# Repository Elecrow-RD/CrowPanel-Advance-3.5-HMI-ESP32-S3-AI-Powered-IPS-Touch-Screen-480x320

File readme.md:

## Menu
### 1, Product picture
### 2, Product version number
### 3, product information
### 4, Use the driver module
### 5,Quick Start
### 6,Folder structure.
### 7,Pin definition
### 8,Guidelines for downloading some of the files from the github repository

### 1, Product picture

### 2, Product version number

|      | Hardware | Software | Remark |
| ---- | -------- | -------- | ------ |
| 1    | V1.0     | V1.0     | old |
| 2    | V1.2     | V1.2     | old |
| 3    | V1.3     | V1.3     | old |
| 4    | V1.4     | V1.3     | latest |

### Version update points:

**V1.2 upgraded**, optimized the amplifier circuit, better sound quality, and use IO21 to control mute. i2s_mic changed to two pins IO9 and IO10 control.

**Version 1.3**,Only the button component has been updated. All other hardware and I/O pins remain the same as in the previous version.

**Version 1.4** is simply an update to the previous version that modifies the packaging of the touchscreen FPC connector. There are no other differences.

### 3, product information

| Main Chip-ESP32-S3-WROOM-1-N16R8     |                                                              |
| -------------------------------------------- | ------------------------------------------------------------ |
| CPU/SoC                                      | high-performance Xtensa 32-bit LX7 dual-core processor, with up to 240MHz |
| System Memory                                | 512KB SRAM、8M PSRAM                                         |
| Memory                                       | 16M Flash，384KB ROM                                         |
| Development Language                         | MicroPython、C/C++                                           |
| Development Environment                      | ESP-IDF、Arduino IDE、PlatformIO、Micro Python         |
| **Screen**                                   |                                                              |
| Size                                         | 3.5 inch                                                     |
| Diver IC                                     | ILI9488                                                      |
| Resolution                                   | 480*320                                                      |
| Display Panel                                | IPS Panel                                                    |
| Touch Panel                                  | Capacitive Single Touch                                      |
| Viewing Angle                                | 178°                                                         |
| Brightness                                   | 400 cd/m²(Typ.)                                              |
| Color Depth                                  | 16-bit                                                       |
| **Wireless Communication - Onboard Antenna** |                                                              |
| WiFi                                         | Support 2.4GHz, 802.11a/b/g/n                                |
| Bluetooth                                    | Support Bluetooth 5.0 and BLE                                |
| Other                                        | **LoRa**                                                     |
| **Interface/Function**                       |                                                              |
| Interface                                    | USB port, UART, I2C, SD card slot, battery socket, speaker port, microphone, etc. |
| Function                                     | RTC clock, audio amplifier, volume control, battery charge management, USB to UART, etc. |
| **Button/LED Indicator**                     |                                                              |
| Reset Button                                 | Yes, press to reset the device                               |
| Boot Button                                  | Yes, press and hold the power button to burn the program     |
| PWR                                          | Power indicator                                              |
| CHG                                          | Lithium battery charging status, completion indication       |
| **Other**                                    |                                                              |
| Installation method                          | Back hanging, fixed hole                                     |
| Operating temperature                        | -20~70 °C                                                    |
| Storage temperature                          | -30~80 °C                                                    |
| Power Input                                  | 5V/2A, USB or UART terminal                                  |
| Dimensions                                   | 101.4\*63.3*15.8mm                                            |

### 4, Use the driver module

| Name   | dependency library                      |
| ------ | --------------------------------------- |
| LVGL   | lvgl/lvgl@8.3.3                         |
| ST7789 | Adafruit GFX Library<br/>version=1.11.0 |

### 5,Quick Start
### Arduino IDE starts

#### Teaching Case Path：./example/example_code3.5

1.Download the library files used by this product to the 'libraries' folder.

C:\Users\Documents\Arduino\libraries\

2.Open the Arduino IDE

3.Open the code configuration environment and burn it

### ESP-IDF starts

#### Teaching Case Path：./example/idf_code

1.Right-click on an empty space in the project folder and select "Open with VS Code" to open the project.

2.In the IDF plug-in, select the port, then compile and flash

### 6,Folder structure.

|--3D file： Contains 3D model files (.stp) for the hardware. These files can be used for visualization, enclosure design, or integration into CAD software.

|--Datasheet: Includes datasheets for components used in the project, providing detailed specifications, electrical characteristics, and pin configurations.

|--Eagle_SCH&PCB: Contains **Eagle CAD** schematic (`.sch`) and PCB layout (`.brd`) files. These are used for circuit design and PCB manufacturing.

|--example: Provides example code and projects to demonstrate how to use the hardware and libraries. These examples help users get started quickly.

|--factory_firmware: Stores pre-compiled factory firmware that can be directly flashed onto the device. This ensures the device runs the default functionality.

|--factory_sourcecode:  Contains the source code for the factory firmware, allowing users to modify and rebuild the firmware as needed.

|--libraries: Includes necessary libraries required for compiling and running the project. These libraries provide drivers and additional functionalities for the hardware.

|--Squareline_studio Instructions for use: Squareline_studio instructions: Demonstrate the use of squareline studio.

### 7,Pin definition

SPIClass* hspi = nullptr;
#define HSPI_MISO  4
#define HSPI_MOSI  6
#define HSPI_SCLK  5
#define HSPI_SS    19

#define SD_MOSI 6
#define SD_MISO 4
#define SD_SCK  5
#define SD_CS   7 //The chip selector pin is not connected to IO

#define I2S_DOUT 12
#define I2S_BCLK 13
#define I2S_LRC 11

cfg.pin_sclk = 42;  // SPIのSCLK

cfg.pin_mosi = 39;  // SPIのCLK

cfg.pin_miso = -1;  // SPIのMISO

cfg.pin_dc = 41; 

#define TOUCH_GT911_SCL 16
#define TOUCH_GT911_SDA 15

### 8,Guidelines for downloading some of the files from the github repository

##### 1, open the link in your browser: https://downgit.github.io/

##### 2, paste the URL of the GitHub destination folder in the input box (example format: `https://github.com/username/repository name/tree/branch name/folder path`)

##### 3, even a that way to download the file.

①Click the “Create Download Link” button to create a download link, copy the link and open it with your browser to download the contents of the corresponding folder directly.

②Click Download, and you can also download it directly.

#### Note: DownGit downloads are stored by default in **your browser's default downloads folder**, usually:

- **Windows**: `C:\Users\your username\Downloads\` (downloads folder)
- **macOS**: `~/Downloads/` (downloads folder)
- **Linux**: `~/Downloads/` (Downloads folder)

If you change the default download path in your browser, the file will be stored in the download location you set. You can find the downloaded file path in your browser's **Download History** (shortcut `Ctrl + J` or `Cmd + J`).

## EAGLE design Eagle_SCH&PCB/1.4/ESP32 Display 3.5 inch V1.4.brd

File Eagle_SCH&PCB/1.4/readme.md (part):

# 3.5-Inch ESP32-S3 Hardware Driver Guide

| Item | Details |
|---|---|
| Document Version | V1.0 |
| Date | 2026-07-30 |
| Author | OpenAI Codex (compiled from project materials) |
| Applicable Hardware | 3.5-inch ESP32 Display / CrowPanel Advance HMI boards |
| Hardware References | `1.4/ESP32 Display 3.5 inch V1.4.sch`, `.brd`, and `ESP32-Display-3.5-inch-V1.4.pdf` |
| Software References | Board-level examples from `lesson-01` through `lesson-08` under `3.5_Arduino` (excluding examples bundled with third-party libraries) |
| Determination Principle | When the schematic conflicts with code that has been successfully tested, the project’s board-level example code takes precedence, and the discrepancy is documented |

> **Important Version Notice**: The directories and filenames identify the hardware as **V1.4**, but the title block in the Eagle schematic and the internal title in the PDF identify it as **V1.2**. This document describes the materials currently available in the repository and does not claim that the two versions are electrically identical. Before production, repair, or porting, the board revision must be confirmed from the PCB silkscreen and/or physical measurements.

## 1. Evidence Levels and Usage

| Level | Meaning | Usage Recommendation |
|---|---|---|
| A - Code Verified | The project’s board-level examples contain explicit pin assignments and success/failure criteria or visible functionality | Use as the primary reference for maintenance and porting |
| B - Schematic and Code Consistent | The schematic nets match the code, but the examples do not cover all edge cases | Usable, but integration testing with the target firmware is still required |
| C - Schematic Confirmed | The component/net exists in the schematic, but the repository contains no corresponding board-level driver test case | Do not claim software verification; additional testing is required |
| D - External Module Example | The code verifies a module connected to an expansion port, not an onboard component | Enable only when the same external module is installed |

“Verified” in this document only means that the repository provides runnable examples and explicit configurations for this board. It does not mean that the physical board was reflashed during the creation of this document.

## 2. System Architecture and Software Stack

- MCU: ESP32-S3-WROOM-1, identified in the schematic as `ESP32-S3-N16R8` (board-level designation indicating 16 MB Flash and 8 MB PSRAM).
- Framework: Arduino-ESP32, supported at the lower level by ESP-IDF peripheral drivers (SPI/I2C/I2S/UART, DMA, and PSRAM). No bare-metal register operations are used.
- Graphics: LovyanGFX + LVGL 9.1.0; LVGL uses two full-screen RGB565 buffers in PSRAM.
- Storage: Arduino `FS`/`SD` on a dedicated SPI bus.
- Audio: ESP32-audioI2S 3.0.12 + Wi-Fi, with output to the onboard NS4168.
- Wireless Expansion: RF24 1.6.1 (nRF24L01) and RadioLib 7.1.0 (SX1262/LoRaWAN).
- Sensor Expansion: Crowbits_DHT20; separate GT911 driver code is also provided for touch input.
- RTOS: Arduino-ESP32 runs FreeRTOS internally, but the project examples do not create custom tasks, queues, or synchronization objects.

## 3. Peripheral Overview

| Category | Peripheral/Component | Key Interface and GPIOs | Status |
|---|---|---|---|
| MCU | ESP32-S3-WROOM-1 | Native USB GPIO19/20; UART0; multiple multiplexed peripherals | B |
| Display | 3.5-inch TFT, configured as ILI9488 in code | SPI2: SCLK42, MOSI39, DC41, CS40; RST2; BL38 | A; RST conflict between schematic and code |
| Touch | Configured as GT911 in code | I2C0: SDA15, SCL16; INT47, RST48; 0x14/400 kHz | A; controller model not identified in schematic |
| Storage | microSD/TF (J5) | MISO4, SCLK5, MOSI6, CS7; SPI at 80 MHz | A/B |
| Audio Output | NS4168 + speaker connector J12 | I2S: LRCLK11, BCLK13, DOUT12; CTRL21 | A/B |
| Microphone | Digital I2S/PDM MIC (MIC1) | CLK9, DATA10; GPIO45 selects the switch path | C |
| Analog Switch | SGM3799 | GPIO9/10 multiplexed between MIC and wireless SPI; SEL=GPIO45 | B |
| Buzzer | Passive buzzer B1 + SS8050 | GPIO8 through NPN low-side driver | C |
| RTC | PCF8563/BM8563 + CR1220 | SDA15, SCL16; common address 0x51 (not verified by code) | C |
| USB-UART | CH340K + automatic download circuit | UART0; DTR/RTS drive EN/BOOT | C (hardware function) |
| Native USB/OTG | Type-C J2 | D-=GPIO19, D+=GPIO20 (through 0 Ω configuration positions) | C |
| USB-UART/Power | Type-C J1 | CH340K USB data, 5 V input | C (hardware function) |
| Battery Charging | TP4059 + PH2.0 battery connector J3 | Autonomous hardware operation; PROG=2 kΩ; CHRG/DONE indicators managed by U14 | C |
| Power Boost | RY3420/HM3416H | Autonomous hardware operation; 45.3 kΩ/10 kΩ feedback; EN connected to VIN | C |
| Charging Indicator Control | STC8G1K08 + red/green LEDs | Monitors CHRG/DONE; not an ESP32-programmable interface | C |
| Backlight/Display Power | NPN backlight switch, optional TFT power switch | BL=GPIO38, active high; GPIO14 path marked NC | A/C |
| Buttons | BOOT K3, RESET K4 | BOOT=GPIO0 active low; RESET=EN active low | C (hardware function) |
| I2C Expansion | J13 HY2.0 | SCL16, SDA15, 3V3, GND | B; shares bus with RTC/touch |
| UART1 Expansion | J15 HY2.0 | ESP TX=GPIO17, ESP RX=GPIO18, 3V3, GND | C |
| UART0 Expansion | J10 | RXD0_H, TXD0_H, 5V, GND | C; shared with download and logging |
| Wireless SPI Expansion | J9/J11 | SCLK10, MISO9, MOSI3, CS0, BUSY46, 3V3/GND | B/D |
| External UART Module | Zigbee example | RX2, TX1, 115200 8N1; GPIO45=LOW | D; multiplexing risk with LCD RST/wireless control |
| External Sensor | DHT20 | I2C SDA15/SCL16; 200 ms read interval | D |
| External Actuator | lesson-03/05 lamp or LED | GPIO18, push-pull output | D; conflicts with UART1 RX |
| External nRF24L01 | RF24 example | SCLK10/MISO9/MOSI3, CE1, CSN2; GPIO45=LOW | D |
| External SX1262 | LoRaWAN example | SCLK10/MISO9/MOSI3, NSS0, DIO1=1, RST2, BUSY46 | D |

## 4. Authoritative GPIO Mapping

| GPIO | Schematic Net/Function | Usage in Successfully Tested Code | Electrical/Multiplexing Notes |
|---:|---|---|---|
| 0 | Wireless CS, BOOT button | SX1262 NSS | Boot strapping pin; a low level from the button affects startup and SPI transactions |
| 1 | UART2 TX net | nRF24 CE; SX1262 DIO1; Zigbee TX | Mutually exclusive across examples; do not initialize simultaneously |
| 2 | UART2 RX net | LCD RST; nRF24 CSN; SX1262 RST; Zigbee RX | Primary conflict point; code takes precedence, but each function requires exclusive use |
| 3 | Wireless SPI MOSI | nRF24/SX1262 MOSI | GPIO45 must select the wireless path |
| 4 | SD MISO | SD MISO | Input with onboard 10 kΩ pull-up |
| 5 | SD SCLK | SD SCLK | Push-pull clock |
| 6 | SD MOSI | SD MOSI | Push-pull data with onboard 10 kΩ pull-up |
| 7 | SD CS | SD CS | Push-pull, idle high, with onboard 10 kΩ pull-up |
| 8 | BEEP | No code | PWM/LEDC recommended; driven through an NPN transistor; polarity and frequency require physical verification |
| 9 | MIC CLK / wireless MISO (SGM3799 COM) | nRF24/SX1262 MISO | Selected by GPIO45; audio recording and wireless SPI cannot be used simultaneously |
| 10 | MIC DATA / wireless SCLK (SGM3799 COM) | nRF24/SX1262 SCLK | Same as above |
| 11 | I2S LRCLK | Audio LRCLK | Push-pull output |
| 12 | I2S SDIN (amplifier data input) | Audio DOUT | Named DOUT in code from the ESP32’s perspective |
| 13 | I2S BCLK | Audio BCLK | Push-pull output |
| 14 | TFT_PWR (components marked NC) | No code | Do not rely on this unless BOM installation of Q11/Q12/R52/R53/R61 is confirmed |
| 15 | I2C SDA | GT911, DHT20, RTC, J13 | Open-drain; schematic shows a 4.7 kΩ pull-up to 3.3 V |
| 16 | I2C SCL | GT911, DHT20, RTC, J13 | Open-drain; schematic shows a 4.7 kΩ pull-up to 3.3 V |
| 17 | UART1 TX | No board-level UART1 example provided | J15 uses 3.3 V logic |
| 18 | UART1 RX | Push-pull output for external lamp/LED | Cannot be used as UART1 RX while GPIO18 is used for the lamp |
| 19 | USB D- | USB Serial/JTAG or OTG | Native USB differential line; do not use as a general-purpose GPIO |
| 20 | USB D+ | USB Serial/JTAG or OTG | Native USB differential line; do not use as a general-purpose GPIO |
| 21 | NS4168 control | Audio amplifier control: initially HIGH, then LOW before playback | Code proves LOW is the operating state; do not assume a conventional active-high EN when porting |
| 38 | LCD backlight | `OUTPUT` + `HIGH` turns it on | Active high through an SS8050 switch; PWM dimming is possible but the frequency must be verified |
| 39 | TFT SDA/MOSI | LCD MOSI | Write-only, no MISO |
| 40 | TFT CS | LCD CS | Push-pull, idle high |
| 41 | TFT RS/D-C | LCD DC | Push-pull |
| 42 | TFT SCK | LCD SCLK | SPI2, 40 MHz writes |
| 45 | SPI/MIC analog switch select | Wireless examples set it to `LOW` | LOW selects the wireless path and disconnects the microphone; stop the bus/microphone clock before changing the level |
| 46 | BOOT_BUSY | SX1262 BUSY; SS placeholder for the nRF24 SPI object | ESP32-S3 boot strapping pin; peripheral power-up levels must not interfere with startup |
| 47 | TP_INT | GT911 INT | Used by LovyanGFX; the auxiliary `touch.h` version sets it to -1 |
| 48 | TP_RST | GT911 RST | Used by LovyanGFX; the auxiliary `touch.h` version sets it to -1 |

## 5. Detailed Onboard Peripheral Descriptions

### 5.1 ESP32-S3 MCU, Flash/PSRAM, and Boot

The schematic component is an ESP32-S3-WROOM-1, with N16R8 shown in the drawing text. The project uses the Arduino API, ESP-IDF SPI/I2C driver types, and `heap_caps_malloc(..., MALLOC_CAP_SPIRAM)`, so the display firmware depends on functional PSRAM.

- Download UART: UART0 connects to the CH340K through a BSS138 level-shifting/isolation network; J10 also exposes `RXD0_H/TXD0_H`.
- Automatic Download: The CH340K’s DTR/RTS signals drive GPIO0/EN through U10.
- Manual Buttons: K3 pulls GPIO0 low (BOOT); K4 pulls EN low (RESET).
- Native USB: GPIO19/20 correspond to D-/D+ and connect to Type-C J2 through 0 Ω configuration positions.
- Serial Examples: lesson-01 uses `Serial.begin(9600)`; most other examples use 115200. Standardize the baud rate when porting to avoid mistaking garbled logs for a hardware failure.

```cpp
Serial.begin(115200);
// PSRAM for the display: each 480x320 RGB565 buffer is approximately 307200 bytes
buf = (lv_color_t *)heap_caps_malloc(sizeof(lv_color_t) * 480 * 320,
                                     MALLOC_CAP_SPIRAM);
```

### 5.2 ILI9488 TFT Display and Backlight

The code explicitly instantiates `lgfx::Panel_ILI9488` using SPI2_HOST, mode 0, and automatic DMA channel selection. The panel’s native memory orientation is 320x480, while the application uses a logical landscape resolution of 480x320.

| Signal | GPIO | Configuration |
|---|---:|---|
| SCLK | 42 | SPI2, 40 MHz write, 16 MHz configured read |
| MOSI/SDA | 39 | Unidirectional write |
| MISO | -1 | Disabled, `readable=false` |
| D/C | 41 | GPIO push-pull |
| CS | 40 | GPIO push-pull |
| RST | 2 (code) | Does not match the schematic; see the conflict matrix |
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
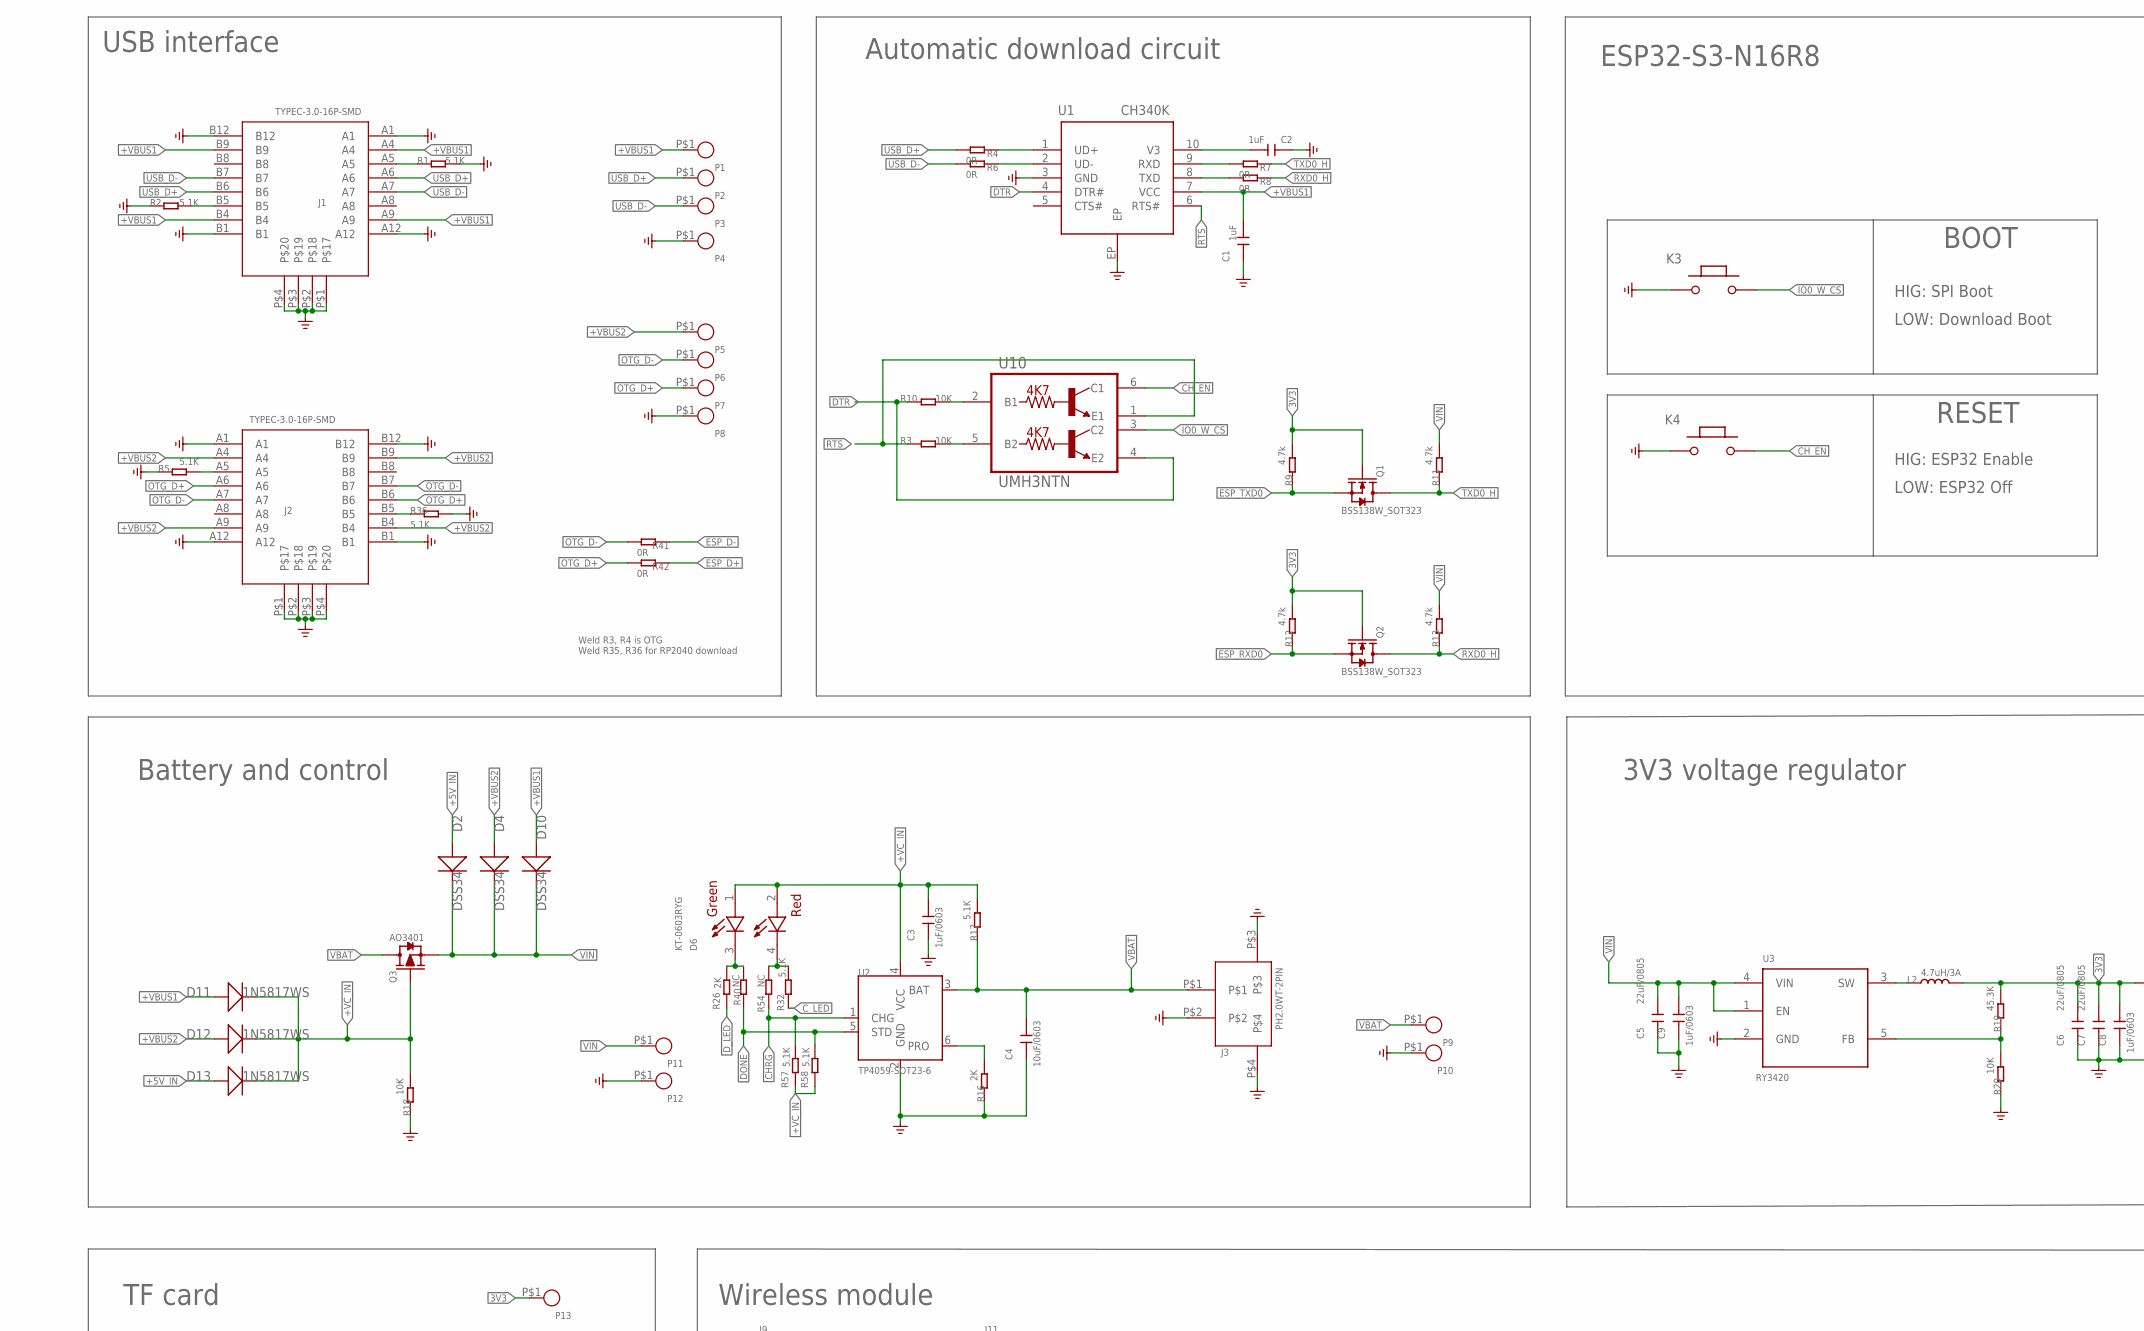
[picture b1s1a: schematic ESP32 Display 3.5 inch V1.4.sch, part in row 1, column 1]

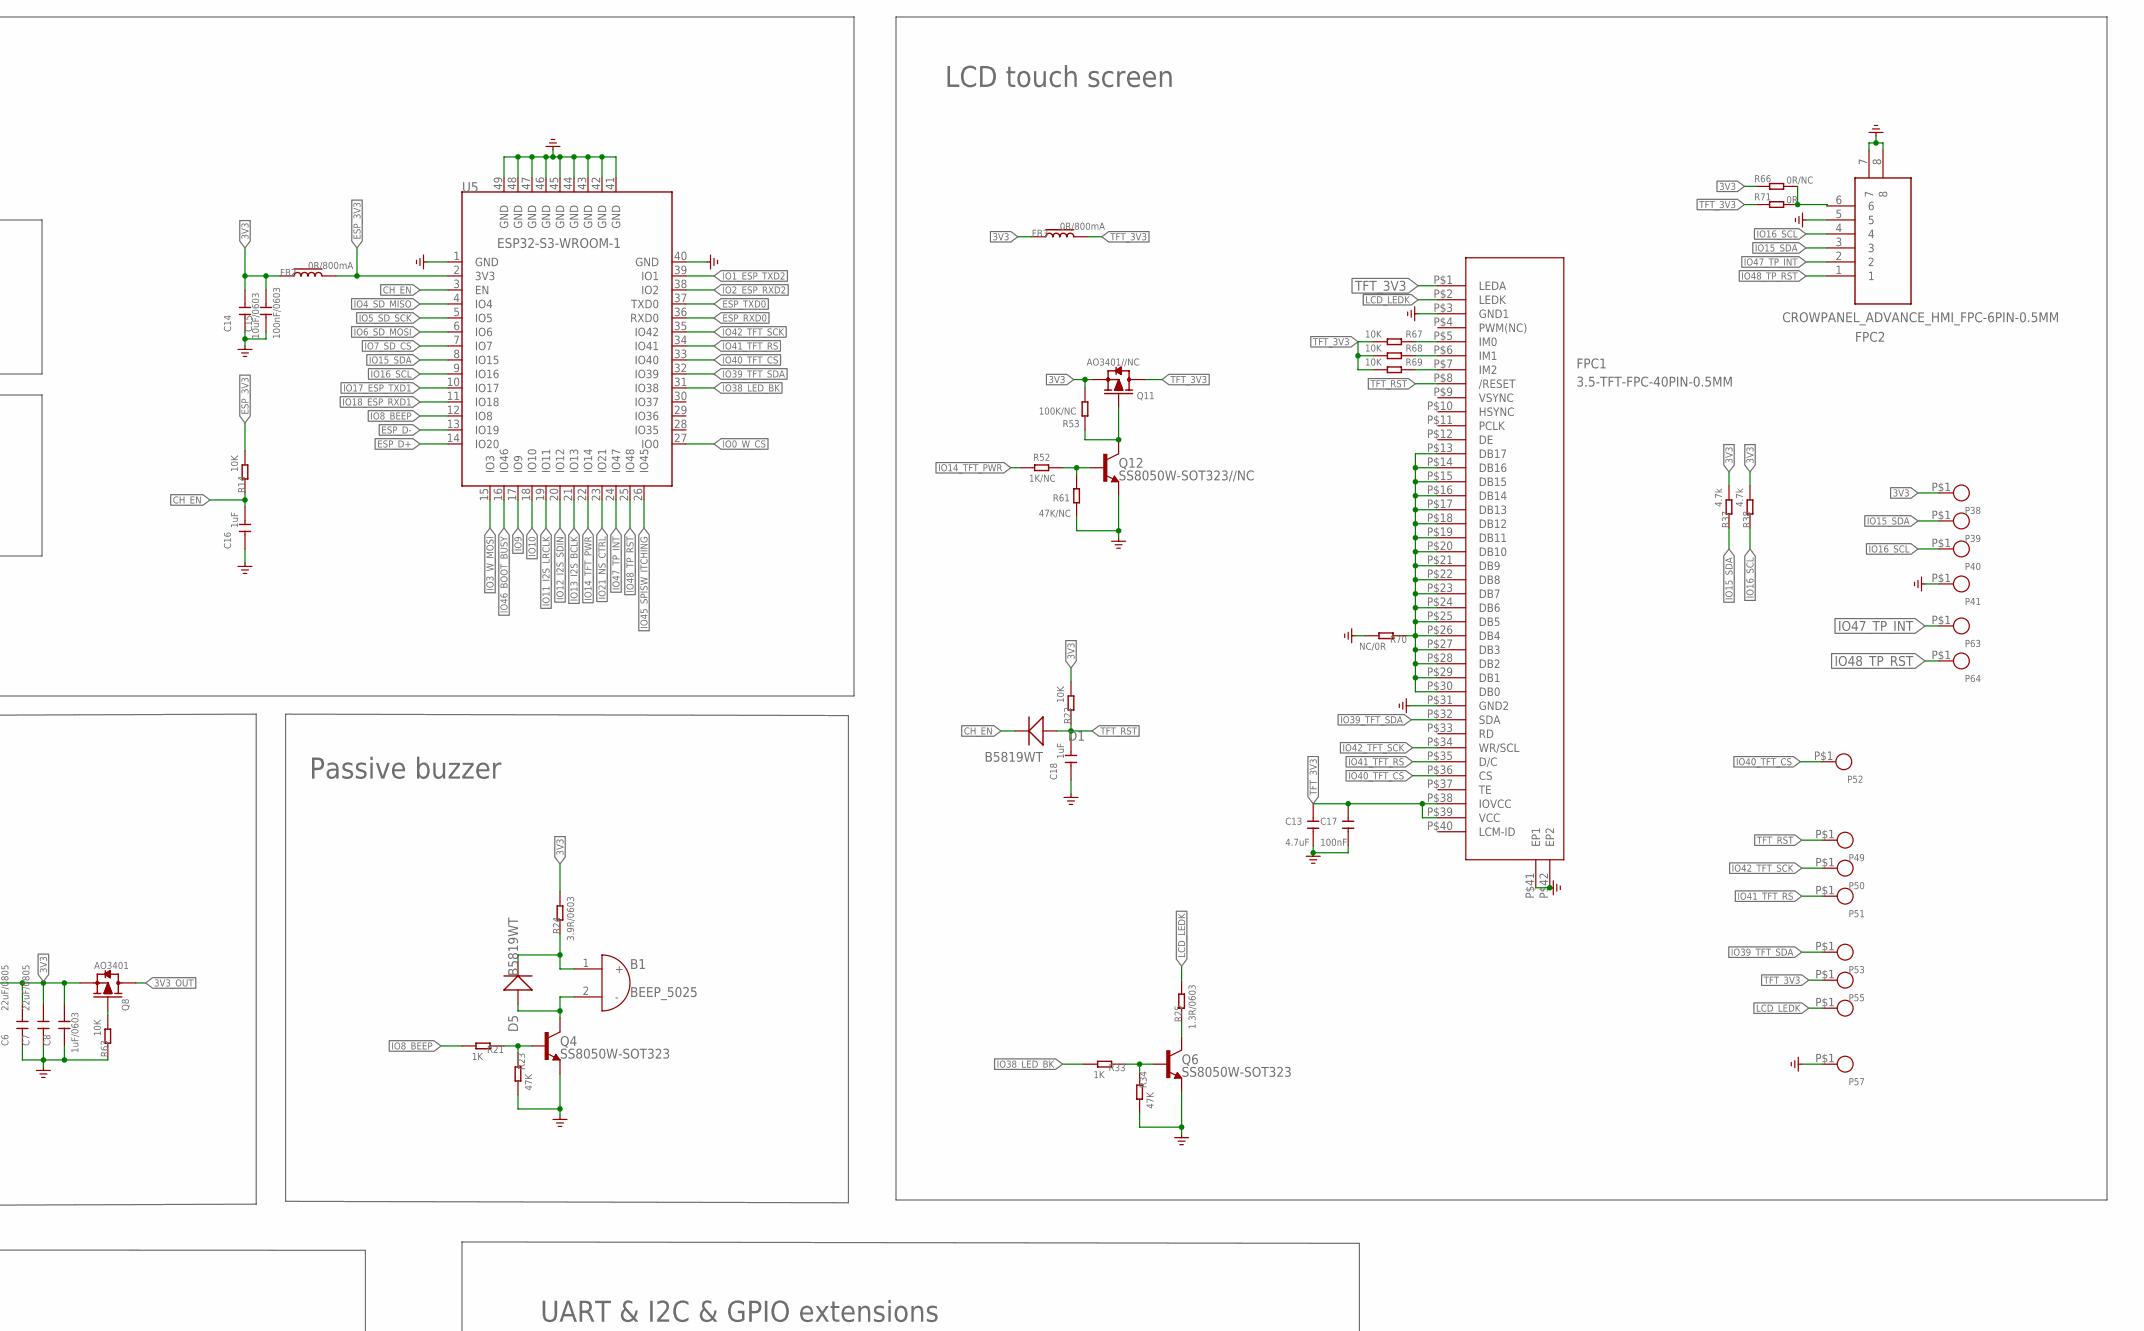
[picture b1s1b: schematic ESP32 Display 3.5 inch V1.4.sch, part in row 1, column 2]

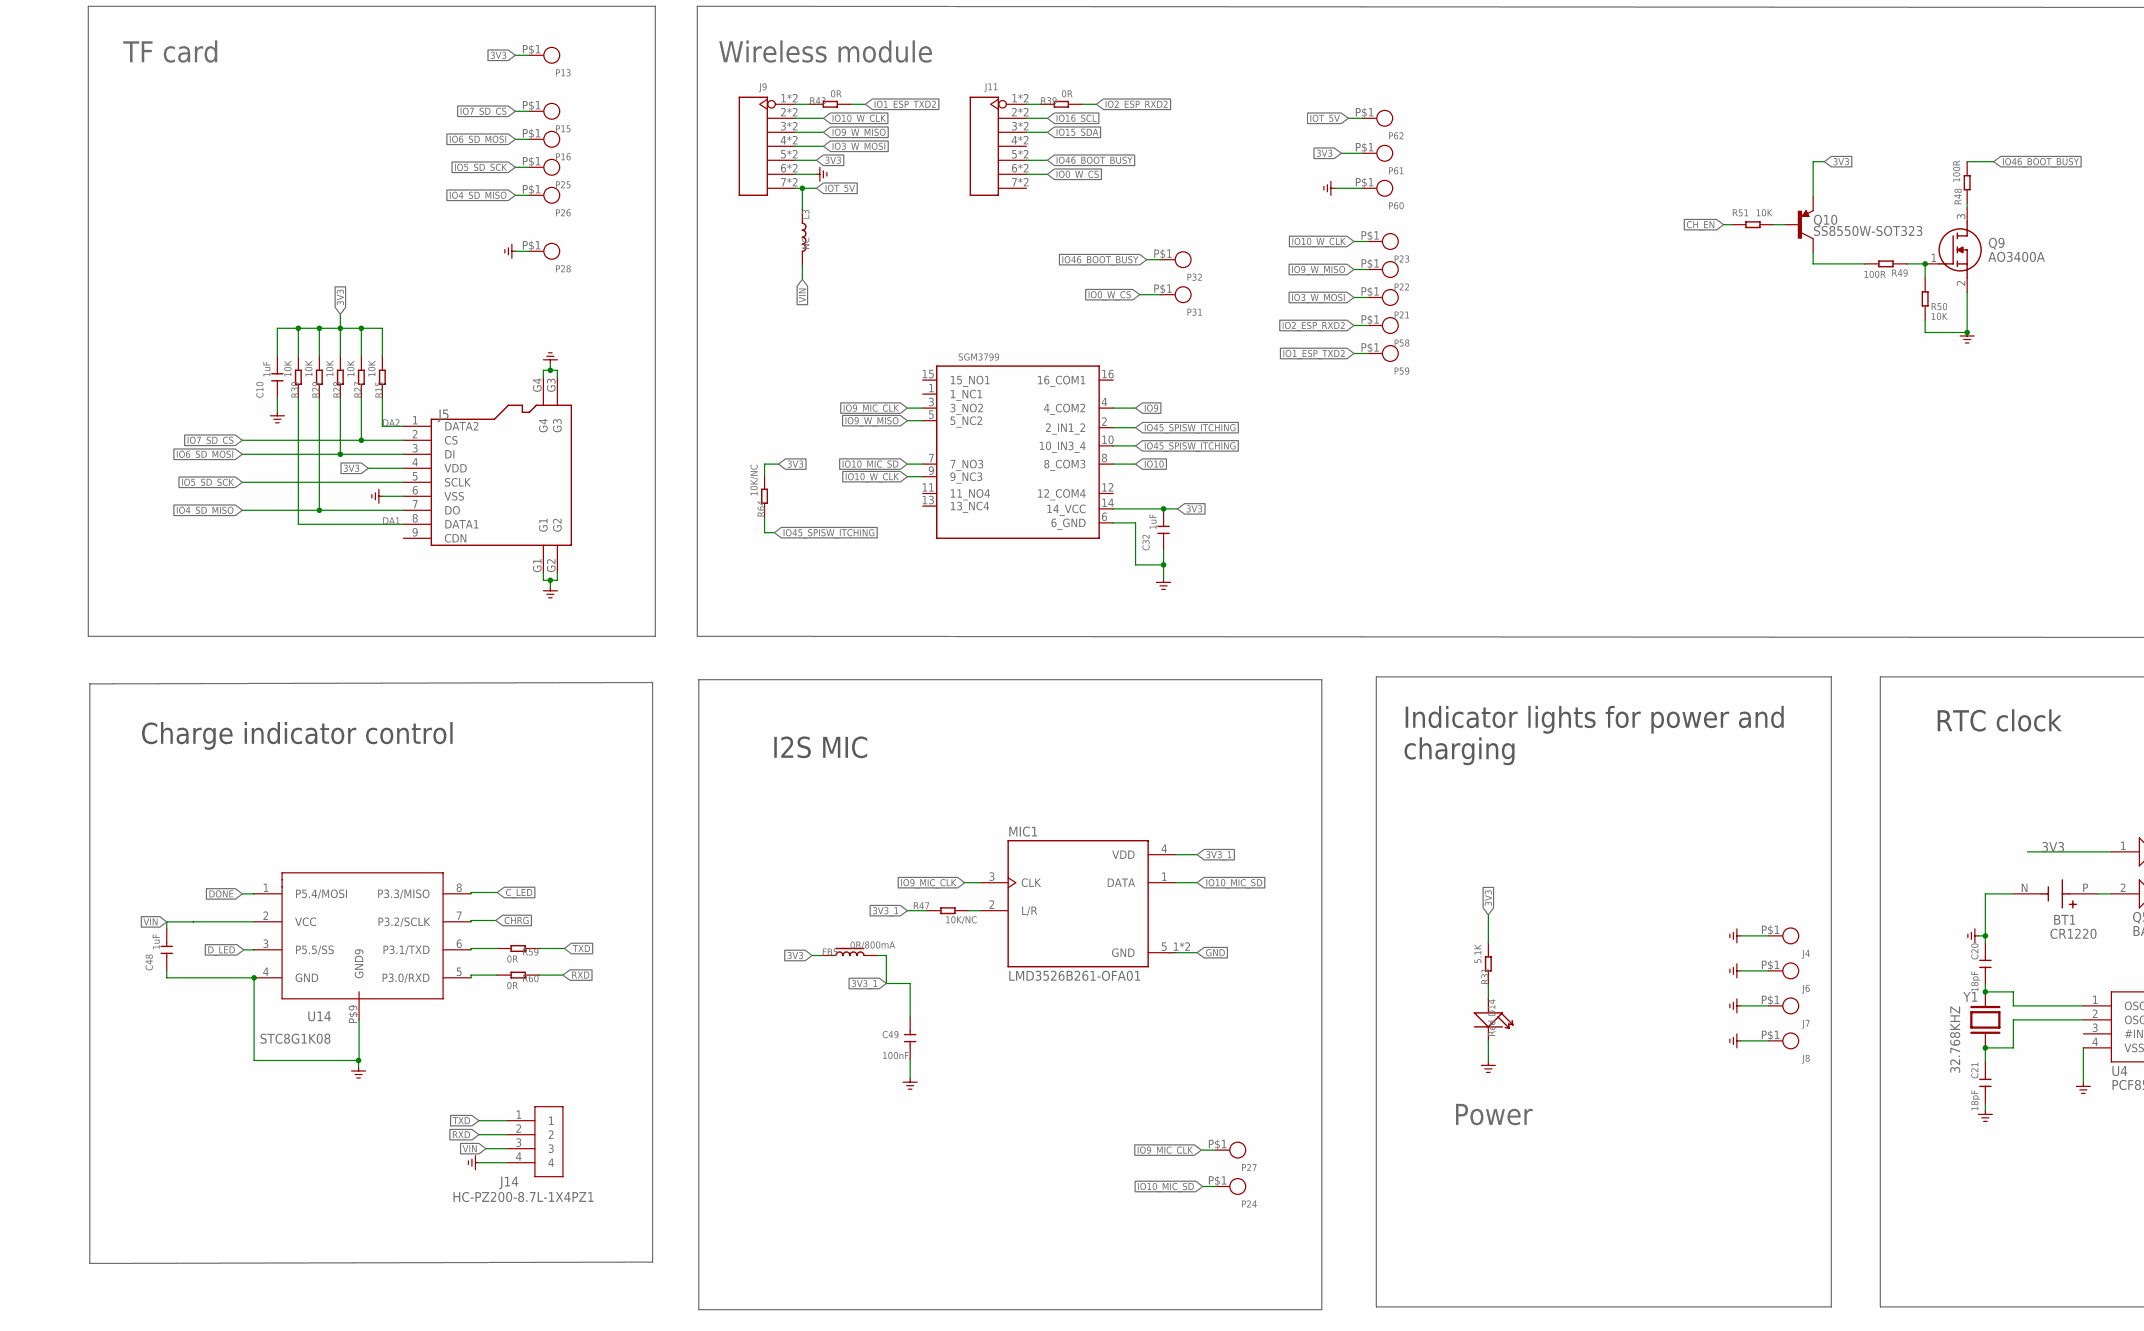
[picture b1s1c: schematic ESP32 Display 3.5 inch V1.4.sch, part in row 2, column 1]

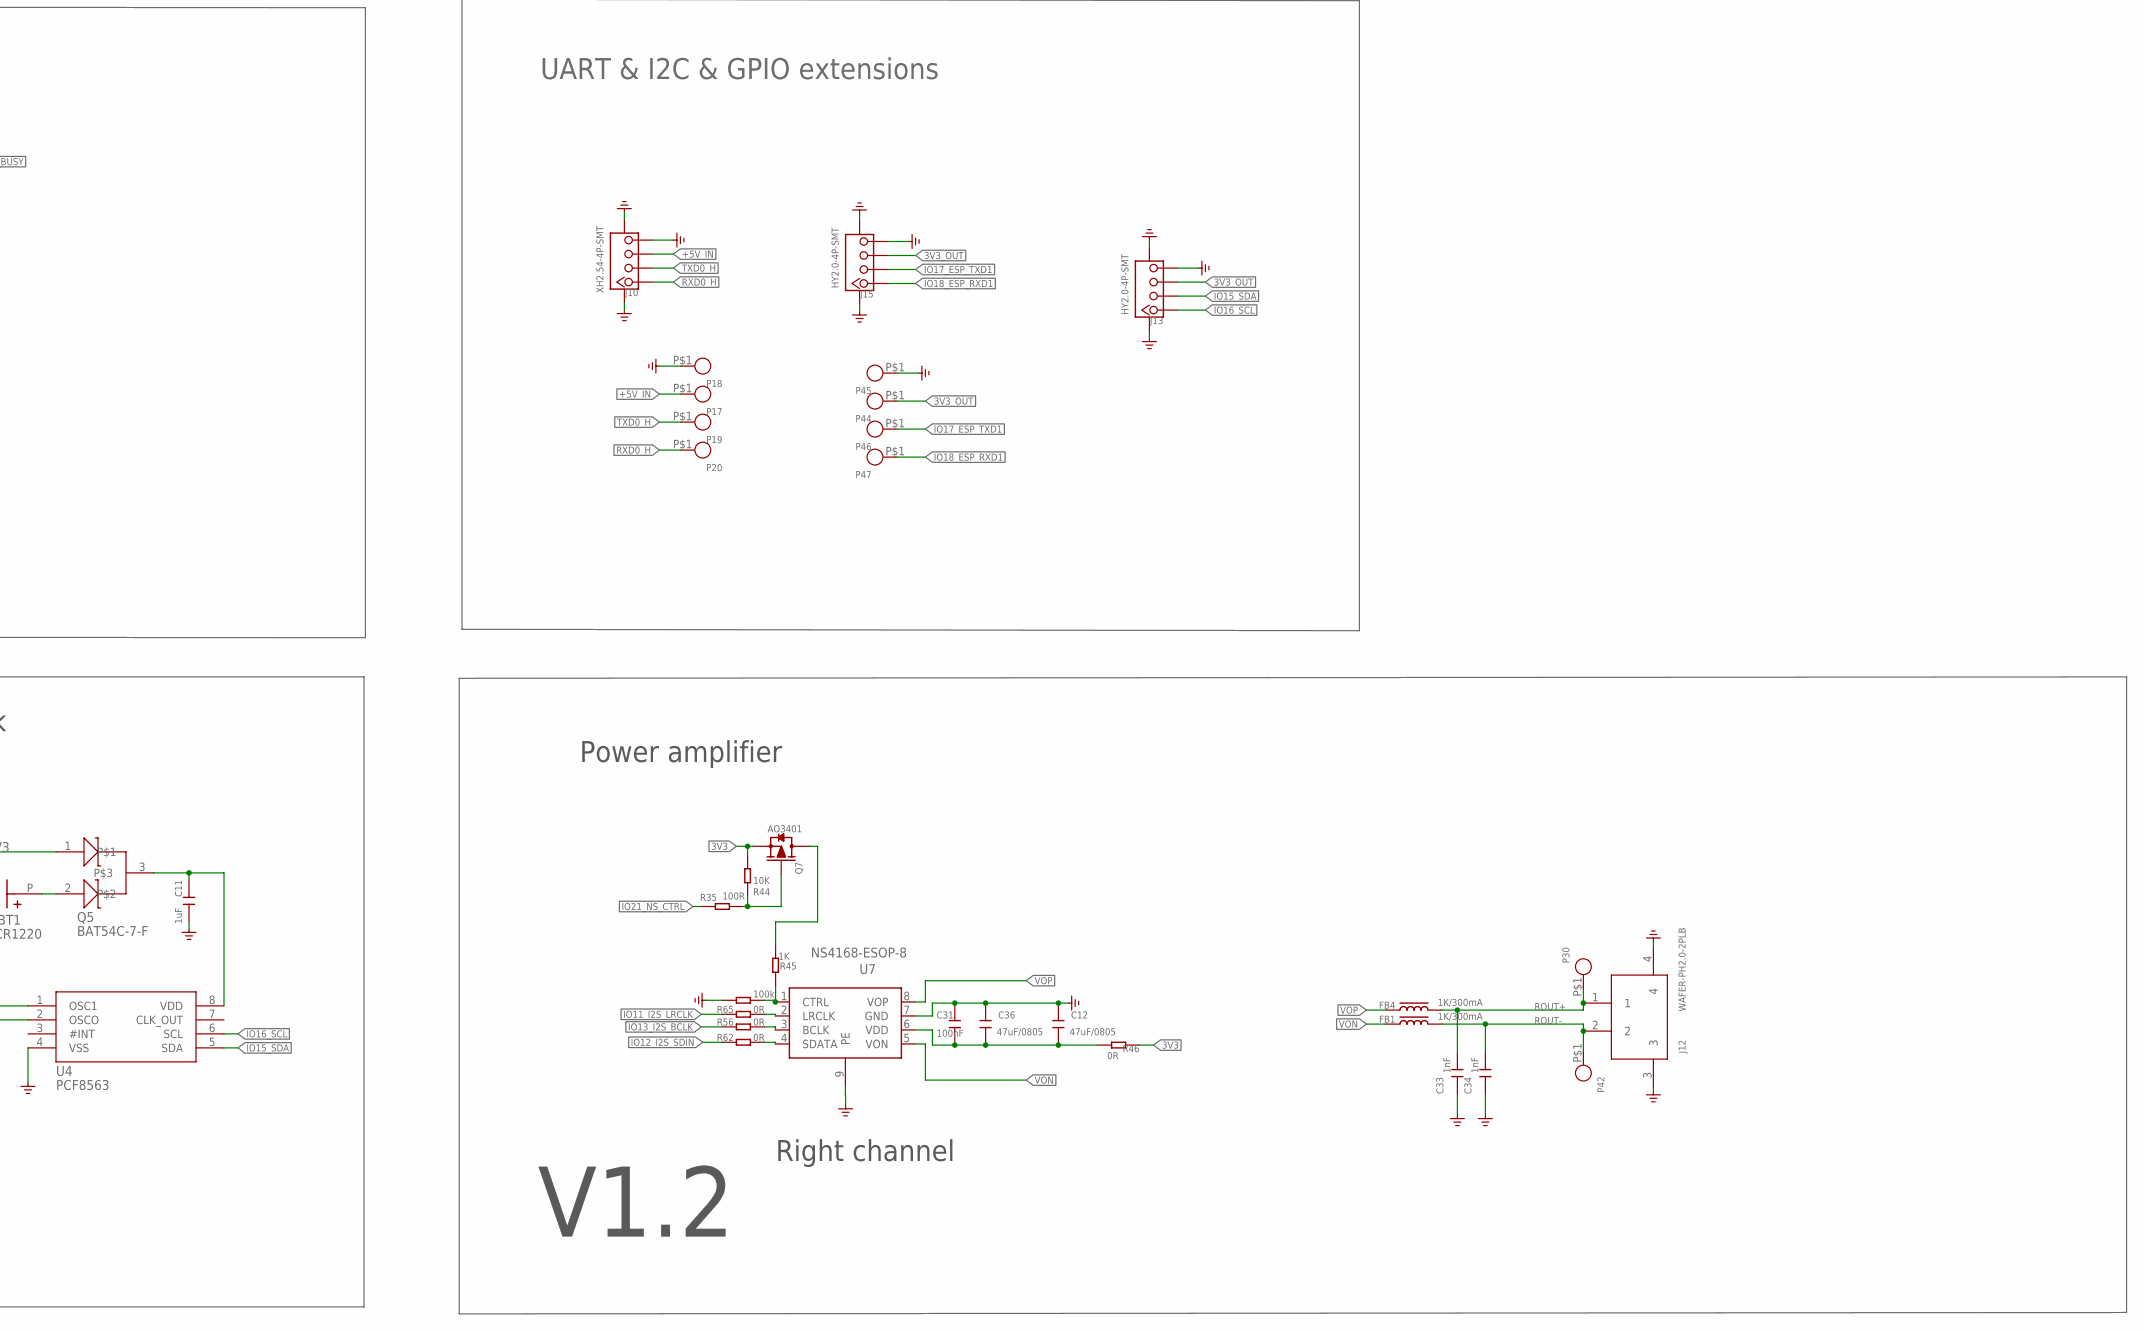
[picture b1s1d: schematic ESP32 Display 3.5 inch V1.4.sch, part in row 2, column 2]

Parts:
B1: BEEP_5025
BT1: CR1220
C1, C2, C10, C11, C16, C18, C32, C48: 1uF; C0402
C3, C8, C9: 1uF/0603; C0603
C4, C14: 10uF/0603; C0603
C5, C6, C7: 22uF/0805; C0805
C12, C36: 47uF/0805; C0805
C13: 4.7uF; C0603
C15: 100nF/0603; C0603
C17, C49: 100nF; C0603
C20, C21: 18pF; C0402
C31: 100nF; C0402
C33, C34: 1nF; C0402
D1, D5: B5819WT; D_SOD523
D2, D4, D10: DSS34; D_SOD123FL
D6: KT-0603RYG; LED_KT-0603RYG
D11, D12, D13: 1N5817WS; D_SOD323
D14: Red; LED0603
FB1, FB4: 1K/300mA; L0603
FB2, FB3, FB5: 0R/800mA; L0603
FPC1: 3.5-TFT-FPC-40PIN-0.5MM; COOPER_0.5MM*40P
FPC2: CROWPANEL_ADVANCE_HMI_FPC-6PIN-0.5MM
J1, J2: TYPEC-3.0-16P-SMD; USB-3.0TYPEC-SMD
J3: PH2.0WT-2PIN
J4, J6, J7, J8: THO-M3.25MM-HOLE; THO-M3.2*5MM-HOLE
J5: HOLDER-MICROSD-9P; 9P-SMD-W/-RING
J9, J11: HEADER-7P-18.28X2.5; H7-2.54-18.28X2.5X5MM
J10: XH2.54-4P-SMT; XH2.54-4P-SMD
J12: WAFER-PH2.0-2PLB; CONN-TH_2P-P2.00_XUNPU_WAFER-PH2.0-2PLB
J13, J15: HY2.0-4P-SMT; CONNECTOR_4P-SMD-2.0
J14: HC-PZ200-8.7L-1X4PZ1; TEST-PIN-4-2.0MM
K3, K4: PB157; 157SW
L2: 4.7uH/3A; L0420
L3: NC; L0603
MIC1: LMD3526B261-OFA01; MIC-SMD_5P-L3.5-W2.7-P1.67
P1, P2, P3, P4, P5, P6, P7, P8, P9, P10, P11, P12, P13, P15, P16, P17, P18, P19, P20, P21, P22, P23, P24, P25, P26, P27, P28, P30, P31, P32, P38, P39, P40, P41, P42, P44, P45, P46, P47, P49, P50, P51, P52, P53, P55, P56, P57, P58, P59, P60, P61, P62, P63, P64: TEST_PADPAD-1.5MM; TEST_PAD-1.5MM
Q1, Q2: BSS138W_SOT323; MOS_SOT323
Q3, Q7, Q8: AO3401; PMOS_SOT23
Q4, Q6: SS8050W-SOT323; MOS_SOT323
Q5: BAT54C-7-F; SOT-23
Q9: AO3400A; SOT95P280X125-3N
Q10: SS8550W-SOT323; MOS_SOT323
Q11: AO3401//NC; PMOS_SOT23
Q12: SS8050W-SOT323//NC; MOS_SOT323
R1, R2, R5, R17, R31, R32, R36, R57, R58: 5.1K; R0402
R3, R10, R14, R15, R18, R20, R22, R27, R28, R29, R30, R44, R50, R51, R63, R67, R68, R69: 10K; R0402
R4, R6, R7, R8, R39, R41, R42, R43, R46, R56, R59, R60, R62, R65, R71: 0R; R0402
R9, R11, R12, R13, R37, R38: 4.7k; R0402
R16, R26: 2K; R0402
R19: 45.3K; R0402
R21, R33, R45: 1K; R0402
R23, R34: 47K; R0402
R24: 3.9R/0603; R0603-SP
R25: 1.3R/0603; R0603-SP
R35, R48, R49: 100R; R0402
R40, R54: NC; R0402
R47, R64: 10K/NC; R0402
R52: 1K/NC; R0402
R53: 100K/NC; R0402
R55: 100k; R0402
R61: 47K/NC; R0402
R66: 0R/NC; R0402
R70: NC/0R; R0402
U1: CH340K; ESOP-10-EP-150MIL
U2: TP4059-SOT23-6; SOT23-6L
U3: RY3420; IC_SOT23-5
U4: PCF8563; MSOP-8
U5: ESP32-S3-WROOM-1; ESP32-S3-WROOM-1-SMD41
U7: NS4168-ESOP-8
U8: SGM3799; IC_SGM3799_TQFN2.6X1.8_16L
U10: UMH3NTN; SOP65P210X100-6N
U14: STC8G1K08; DFN8
Y1: 32.768KHZ; SMD3215-2P

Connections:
3V3: C6.2, C7.2, C8.2, C10.2, C14.2, C15.2, C32.2, FB2.1, FB3.1, FB5.1, J5.4 (VDD), J9.5, J9.5-5 (5), L2.2, P13.P$1, P38.P$1, P61.P$1, Q1.1 (G), Q2.1 (G), Q5.1, Q7.2 (S), Q8.2 (S), Q10.2 (E), Q11.2 (S), R9.2, R12.2, R15.2, R19.2, R22.2, R24.2, R27.2, R28.2, R29.2, R30.2, R31.2, R37.2, R38.2, R44.2, R46.1, R53.2, R64.2, R66.2, U8.14 (14_VCC)
3V3_1: C49.2, FB5.2, MIC1.4 (VDD), R47.2
3V3_OUT: J13.3, J15.3, P44.P$1, Q8.3 (D)
+5V_IN: D2.+, D13.+, J10.3, P17.P$1
+VBUS1: C1.2, D10.+, D11.+, J1.A4, J1.A9, J1.B4, J1.B9, P1.P$1, U1.7 (VCC)
+VBUS2: D4.+, D12.+, J2.A4, J2.A9, J2.B4, J2.B9, P5.P$1
+VC_IN: C3.2, D6.1, D6.2, D11.-, D12.-, D13.-, Q3.1 (G), R17.2, R18.2, R57.1, R58.1, U2.4 (VCC)
CHRG: R54.1, R57.2, U2.1 (CHG), U14.7 (P3.2/SCLK)
CH_EN: C16.2, D1.-, K4.2, R14.1, R51.1, U5.3 (EN), U10.6 (C1)
C_LED: R32.1, U14.8 (P3.3/MISO)
DA1: J5.8 (DATA1), R30.1
DA2: J5.1 (DATA2), R15.1
DONE: R40.1, R58.2, U2.5 (STD), U14.1 (P5.4/MOSI)
DTR: R10.2, U1.4 (DTR#), U10.4 (E2)
D_LED: R26.1, U14.3 (P5.5/SS)
ESP_3V3: FB2.2, R14.2, U5.2 (3V3)
ESP_D+: R42.1, U5.14 (IO20)
ESP_D-: R41.1, U5.13 (IO19)
ESP_RXD0: Q2.2 (S), R12.1, U5.36 (RXD0)
ESP_TXD0: Q1.2 (S), R9.1, U5.37 (TXD0)
GND: BT1.N (-), C1.1, C2.1, C3.1, C4.1, C5.1, C6.1, C7.1, C8.1, C9.1, C10.1, C11.2, C12.2, C13.1, C14.1, C15.1, C16.1, C17.1, C18.1, C20.1, C21.2, C31.2, C32.1, C33.1, C34.1, C36.2, C48.1, C49.1, D14.-, FPC1.P$3 (GND1), FPC1.P$31 (GND2), FPC1.P$41 (EP1), FPC1.P$42 (EP2), FPC2.5, FPC2.7, FPC2.8, J1.A1, J1.A12, J1.B1, J1.B12, J1.P$1, J1.P$2, J1.P$3, J1.P$4, J2.A1, J2.A12, J2.B1, J2.B12, J2.P$1, J2.P$2, J2.P$3, J2.P$4, J3.P$2, J3.P$3, J3.P$4, J4.P$1, J5.6 (VSS), J5.G1, J5.G2, J5.G3, J5.G4, J6.P$1, J7.P$1, J8.P$1, J9.6, J9.6-6 (6), J10.4, J10.5 (SS1), J10.6 (SS2), J12.3, J12.4, J13.4, J13.SS1, J13.SS2, J14.4, J15.4, J15.SS1, J15.SS2, K3.1, K4.1, MIC1.5_1 (GND), MIC1.5_2 (GND), P4.P$1, P8.P$1, P10.P$1, P12.P$1, P18.P$1, P28.P$1, P41.P$1, P45.P$1, P57.P$1, P60.P$1, Q4.2 (E), Q6.2 (E), Q9.2 (S), Q12.2 (E), R1.2, R2.1, R5.1, R16.1, R18.1, R20.1, R23.2, R34.2, R36.2, R50.2, R55.2, R61.2, R63.1, R70.2, U1.3 (GND), U1.EP, U2.2 (GND), U3.2 (GND), U4.4 (VSS), U5.1 (GND), U5.40 (GND), U5.41 (GND), U5.42 (GND), U5.43 (GND), U5.44 (GND), U5.45 (GND), U5.46 (GND), U5.47 (GND), U5.48 (GND), U5.49 (GND), U7.7 (GND), U7.9 (PE), U8.6 (6_GND), U14.4 (GND), U14.P$9 (GND9)
IO0_W_CS: J11.6, J11.6-6 (6), K3.2, P31.P$1, U5.27 (IO0), U10.3 (C2)
IO1_ESP_TXD2: P59.P$1, R43.2, U5.39 (IO1)
IO2_ESP_RXD2: P58.P$1, R39.2, U5.38 (IO2)
IO3_W_MOSI: J9.4, J9.4-4 (4), P21.P$1, U5.15 (IO3)
IO4_SD_MISO: J5.7 (DO), P26.P$1, R29.1, U5.4 (IO4)
IO5_SD_SCK: J5.5 (SCLK), P25.P$1, U5.5 (IO5)
IO6_SD_MOSI: J5.3 (DI), P16.P$1, R28.1, U5.6 (IO6)
IO7_SD_CS: J5.2 (CS), P15.P$1, R27.1, U5.7 (IO7)
IO8_BEEP: R21.2, U5.12 (IO8)
IO9: U5.17 (IO9), U8.4 (4_COM2)
IO9_MIC_CLK: MIC1.3 (CLK), P27.P$1, U8.3 (3_NO2)
IO9_W_MISO: J9.3, J9.3-3 (3), P22.P$1, U8.5 (5_NC2)
IO10: U5.18 (IO10), U8.8 (8_COM3)
IO10_MIC_SD: MIC1.1 (DATA), P24.P$1, U8.7 (7_NO3)
IO10_W_CLK: J9.2, J9.2-2 (2), P23.P$1, U8.9 (9_NC3)
IO11_I2S_LRCLK: R65.2, U5.19 (IO11)
IO12_I2S_SDIN: R62.2, U5.20 (IO12)
IO13_I2S_BCLK: R56.2, U5.21 (IO13)
IO14_TFT_PWR: R52.2, U5.22 (IO14)
IO15_SDA: FPC2.3, J11.3, J11.3-3 (3), J13.2, P39.P$1, R37.1, U4.5 (SDA), U5.8 (IO15)
IO16_SCL: FPC2.4, J11.2, J11.2-2 (2), J13.1, P40.P$1, R38.1, U4.6 (SCL), U5.9 (IO16)
IO17_ESP_TXD1: J15.2, P46.P$1, U5.10 (IO17)
IO18_ESP_RXD1: J15.1, P47.P$1, U5.11 (IO18)
IO21_NS_CTRL: R35.1, U5.23 (IO21)
IO38_LED_BK: R33.2, U5.31 (IO38)
IO39_TFT_SDA: FPC1.P$32 (SDA), P53.P$1, U5.32 (IO39)
IO40_TFT_CS: FPC1.P$36 (CS), P52.P$1, U5.33 (IO40)
IO41_TFT_RS: FPC1.P$35 (D/C), P51.P$1, U5.34 (IO41)
IO42_TFT_SCK: FPC1.P$34 (WR/SCL), P50.P$1, U5.35 (IO42)
IO45_SPISW_ITCHING: R64.1, U5.26 (IO45), U8.2 (2_IN1_2), U8.10 (10_IN3_4)
IO46_BOOT_BUSY: J11.5, J11.5-5 (5), P32.P$1, R48.2, U5.16 (IO46)
IO47_TP_INT: FPC2.2, P63.P$1, U5.24 (IO47)
IO48_TP_RST: FPC2.1, P64.P$1, U5.25 (IO48)
IOT_5V: J9.7, J9.7-7 (7), L3.1, P62.P$1
LCD_LEDK: FPC1.P$2 (LEDK), P56.P$1, R25.2
unnamed: J1.A5, R1.1
unnamed: Q7.1 (G), R35.2, R44.1
unnamed: J2.B5, R36.1
unnamed: J2.A5, R5.2
unnamed: R4.1, U1.1 (UD+)
unnamed: R6.1, U1.2 (UD-)
unnamed: R10.1, U10.2 (B1)
unnamed: R3.1, U10.5 (B2)
unnamed: C2.2, U1.10 (V3)
unnamed: R7.2, U1.9 (RXD)
unnamed: R8.2, U1.8 (TXD)
unnamed: R16.2, U2.6 (PRO)
unnamed: L2.1, U3.3 (SW)
unnamed: Q4.1 (B), R21.1, R23.1
unnamed: B1.2 (-), D5.+, Q4.3 (C)
unnamed: B1.1 (+), D5.-, R24.1
unnamed: MIC1.2 (L/R), R47.1
unnamed: BT1.P (+), Q5.2
unnamed: R59.2, U14.6 (P3.1/TXD)
unnamed: R60.2, U14.5 (P3.0/RXD)
unnamed: D14.+, R31.1
unnamed: Q6.3 (C), R25.1
unnamed: J9.1, J9.1-1 (1), R43.1
unnamed: J11.1, J11.1-1 (1), R39.1
unnamed: C11.1, Q5.3, U4.8 (VDD)
unnamed: C21.1, U4.2 (OSCO), Y1.2
unnamed: Q8.1 (G), R63.2
unnamed: Q9.1 (G), R49.1, R50.1
unnamed: Q6.1 (B), R33.1, R34.1
unnamed: C20.2, U4.1 (OSC1), Y1.1
unnamed: R19.1, R20.2, U3.5 (FB)
unnamed: Q10.3 (C), R49.2
unnamed: FPC1.P$5 (IM0), R67.1
unnamed: Q10.1 (B), R51.2
unnamed: Q11.1 (G), Q12.3 (C), R53.1
unnamed: Q12.1 (B), R52.1, R61.1
unnamed: FPC2.6, R66.1, R71.1
unnamed: R65.1, U7.2 (LRCLK)
unnamed: D6.3, R26.2, R40.2
unnamed: FPC1.P$6 (IM1), R68.1
unnamed: FPC1.P$7 (IM2), R69.1
unnamed: D6.4, R32.2, R54.2
unnamed: FPC1.P$13 (DB17), FPC1.P$14 (DB16), FPC1.P$15 (DB15), FPC1.P$16 (DB14), FPC1.P$17 (DB13), FPC1.P$18 (DB12), FPC1.P$19 (DB11), FPC1.P$20 (DB10), FPC1.P$21 (DB9), FPC1.P$22 (DB8), FPC1.P$23 (DB7), FPC1.P$24 (DB6), FPC1.P$25 (DB5), FPC1.P$26 (DB4), FPC1.P$27 (DB3), FPC1.P$28 (DB2), FPC1.P$29 (DB1), FPC1.P$30 (DB0), R70.1
unnamed: R56.1, U7.3 (BCLK)
unnamed: R62.1, U7.4 (SDATA)
unnamed: C12.1, C31.1, C36.1, R46.2, U7.6 (VDD)
unnamed: J1.B5, R2.2
unnamed: Q9.3 (D), R48.1
NS_3V3: Q7.3 (D), R45.1
NS_CTRL: R45.2, R55.1, U7.1 (CTRL)
OTG_D+: J2.A6, J2.B6, P7.P$1, R42.2
OTG_D-: J2.A7, J2.B7, P6.P$1, R41.2
ROUT+: C33.2, FB4.2, J12.1, P30.P$1
ROUT-: C34.2, FB1.2, J12.2, P42.P$1
RTS: R3.2, U1.6 (RTS#), U10.1 (E1)
RXD: J14.2, R60.1
RXD0_H: J10.1, P20.P$1, Q2.3 (D), R8.1, R13.1
TFT_3V3: C13.2, C17.2, FB3.2, FPC1.P$1 (LEDA), FPC1.P$38 (IOVCC), FPC1.P$39 (VCC), P55.P$1, Q11.3 (D), R67.2, R68.2, R69.2, R71.2
TFT_RST: C18.2, D1.+, FPC1.P$8 (/RESET), P49.P$1, R22.1
TXD: J14.1, R59.1
TXD0_H: J10.2, P19.P$1, Q1.3 (D), R7.1, R11.1
USB_D+: J1.A6, J1.B6, P2.P$1, R4.2
USB_D-: J1.A7, J1.B7, P3.P$1, R6.2
VBAT: C4.2, J3.P$1, P9.P$1, Q3.3 (D), R17.1, U2.3 (BAT)
VIN: C5.2, C9.2, C48.2, D2.-, D4.-, D10.-, J14.3, L3.2, P11.P$1, Q3.2 (S), R11.2, R13.2, U3.1 (EN), U3.4 (VIN), U14.2 (VCC)
VON: FB1.1, U7.5 (VON)
VOP: FB4.1, U7.8 (VOP)

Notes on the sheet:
BOOT
RESET
HIG: SPI Boot
LOW: Download Boot
HIG: ESP32 Enable
LOW: ESP32 Off
Power
USB interface
Automatic download circuit
Battery and control
RTC clock
Weld R3, R4 is OTG Weld R35, R36 for RP2040 download
ESP32-S3-N16R8
LCD touch screen
Passive buzzer
3V3 voltage regulator
TF card
Wireless module
UART & I2C & GPIO extensions
Indicator lights for power and charging
Charge indicator control
I2S MIC
Power amplifier
Right channel
V1.2
